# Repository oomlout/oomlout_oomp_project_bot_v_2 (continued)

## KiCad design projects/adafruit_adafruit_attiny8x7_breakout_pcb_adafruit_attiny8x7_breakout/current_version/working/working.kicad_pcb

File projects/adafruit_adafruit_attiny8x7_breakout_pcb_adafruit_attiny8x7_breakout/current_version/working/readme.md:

# adafruit_attiny8x7_breakout_pcb
 
## summary 
* id: adafruit_adafruit_attiny8x7_breakout_pcb_adafruit_attiny8x7_breakout
* user: adafruit
* name: adafruit_attiny8x7_breakout_pcb
* board: adafruit_attiny8x7_breakout
* repo: https://github.com/adafruit/Adafruit-ATtiny8x7-Breakout-PCB

* src_file_repo_sch: 
* src_file_repo_sch_link: https://github.com/adafruit/Adafruit-ATtiny8x7-Breakout-PCB/tree/main/
* full details link: https://github.com/oomlout/oomlout_oomp_project_bot_v_2/tree/main/projects/adafruit_adafruit_attiny8x7_breakout_pcb_adafruit_attiny8x7_breakout/current_version/working  

## schematic  
  
[schematic (pdf)](working_schematic.pdf) 

## pcb  

[board (pdf)](working.pdf)  

## working_bom
| Id | Designator | Footprint | Quantity | Designation | Supplier and ref |  | None | 
| --- | --- | --- | --- | --- | --- | --- | --- | 
| 1 | C5 | 0603-NO | 1 | 0.1uF |  |  | [''] | 
| 2 | U1 | SOT23-5 | 1 | ap2112 |  |  | [''] | 
| 3 | JP3,JP1 | 1X12_ROUND_76MIL | 2 |  |  |  | [''] | 
| 4 | C1 | 0805_10MGAP | 1 | 10uF |  |  | [''] | 
| 5 | R6 | RESPACK_4X0603 | 1 | 10K |  |  | [''] | 
| 6 | D3 | CHIPLED_0603_NOOUTLINE | 1 | GREEN |  |  | [''] | 
| 7 | C3 | 0805-NO | 1 | 10uF |  |  | [''] | 
| 8 | IC2 | QFN24_4MM | 1 | ATTINY8X7-MU |  |  | [''] | 
| 9 | U$12 | PCBFEAT-REV-040 | 1 |  |  |  | [''] | 
| 10 | R1 | 0603-NO | 1 | 10k |  |  | [''] | 
| 11 | CONN3,CONN4 | JST_SH4 | 2 | STEMMA_I2C_QT |  |  | [''] | 
| 12 | D4 | CHIPLED_0603_NOOUTLINE | 1 | red |  |  | [''] | 
| 13 | U$7 | SEESAW_LOGO | 1 |  |  |  | [''] | 
| 14 | SJ1 | SOLDERJUMPER_2WAY_OPEN_NOPASTE | 1 |  |  |  | [''] | 

## bom_schematic
| Ref | Qnty | Value | Cmp name | Footprint | Description | Vendor | DNP | 
| --- | --- | --- | --- | --- | --- | --- | --- | 
| C1 | 1 | 10uF | CAP_CERAMIC0805_10MGAP | working:0805_10MGAP |  |  |  | 
| C3 | 1 | 10uF | CAP_CERAMIC0805-NOOUTLINE | working:0805-NO |  |  |  | 
| C5 | 1 | 0.1uF | CAP_CERAMIC0603_NO | working:0603-NO |  |  |  | 
| CONN3, CONN4 | 2 | STEMMA_I2C_QT | STEMMA_I2C_QT | working:JST_SH4 |  |  |  | 
| D3 | 1 | GREEN | LED0603_NOOUTLINE | working:CHIPLED_0603_NOOUTLINE |  |  |  | 
| D4 | 1 | red | LED0603_NOOUTLINE | working:CHIPLED_0603_NOOUTLINE |  |  |  | 
| IC2 | 1 | ATTINY8X7-MU | ATTINY8X7-MU | working:QFN24_4MM |  |  |  | 
| JP1, JP3 | 2 | HEADER-1X1276MIL | HEADER-1X1276MIL | working:1X12_ROUND_76MIL |  |  |  | 
| R1 | 1 | 10k | RESISTOR_0603_NOOUT | working:0603-NO |  |  |  | 
| R6 | 1 | 10K | RESISTOR_4PACK | working:RESPACK_4X0603 |  |  |  | 
| SJ1 | 1 | SOLDERJUMPER_2WAY | SOLDERJUMPER_2WAY | working:SOLDERJUMPER_2WAY_OPEN_NOPASTE |  |  |  | 
| U1 | 1 | ap2112 | VREG_SOT23-5 | working:SOT23-5 |  |  |  |

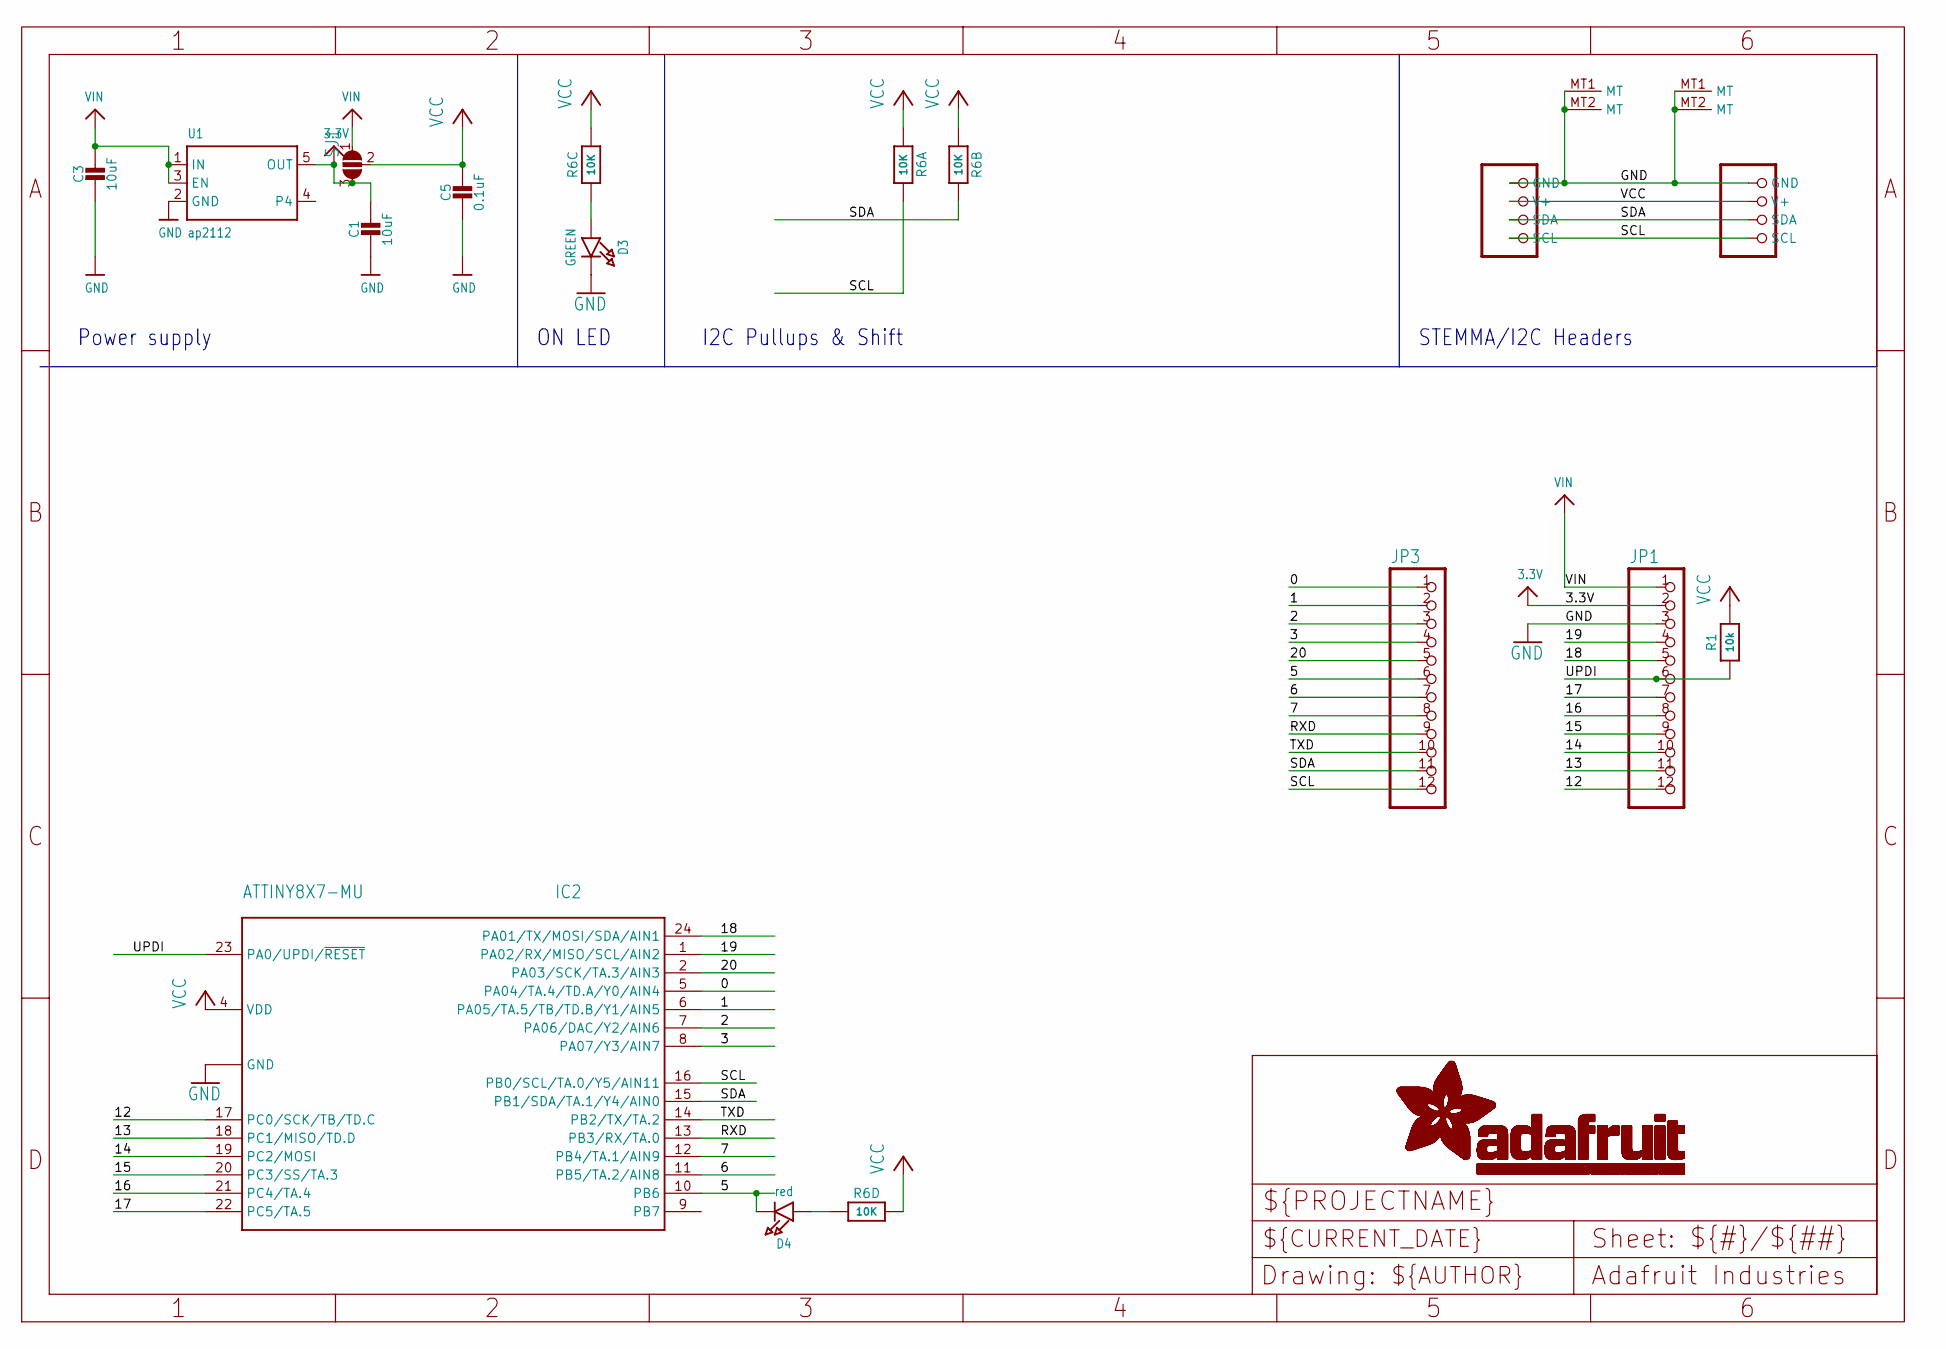
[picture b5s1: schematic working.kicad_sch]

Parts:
C1: 10uF; 0805_10MGAP
C3: 10uF; 0805-NO
C5: 0.1uF; 0603-NO
CONN3, CONN4: STEMMA_I2C_QT; JST_SH4
D3: GREEN; CHIPLED_0603_NOOUTLINE
D4: red; CHIPLED_0603_NOOUTLINE
IC2: ATTINY8X7-MU; QFN24_4MM
JP1, JP3: HEADER-1X1276MIL; 1X12_ROUND_76MIL
R1: 10k; 0603-NO
R6: 10K; RESPACK_4X0603
SJ1: SOLDERJUMPER_2WAY; SOLDERJUMPER_2WAY_OPEN_NOPASTE
U1: ap2112; SOT23-5

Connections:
0: IC2.5 (PA04/TA.4/TD.A/Y0/AIN4), JP3.1
1: IC2.6 (PA05/TA.5/TB/TD.B/Y1/AIN5), JP3.2
2: IC2.7 (PA06/DAC/Y2/AIN6), JP3.3
3: IC2.8 (PA07/Y3/AIN7), JP3.4
3.3V: C1.1, JP1.2, SJ1.3, U1.5 (OUT)
5: D4.C, IC2.10 (PB6), JP3.6
6: IC2.11 (PB5/TA.2/AIN8), JP3.7
7: IC2.12 (PB4/TA.1/AIN9), JP3.8
12: IC2.17 (PC0/SCK/TB/TD.C), JP1.12
13: IC2.18 (PC1/MISO/TD.D), JP1.11
14: IC2.19 (PC2/MOSI), JP1.10
15: IC2.20 (PC3/SS/TA.3), JP1.9
16: IC2.21 (PC4/TA.4), JP1.8
17: IC2.22 (PC5/TA.5), JP1.7
18: IC2.24 (PA01/TX/MOSI/SDA/AIN1), JP1.5
19: IC2.1 (PA02/RX/MISO/SCL/AIN2), JP1.4
20: IC2.2 (PA03/SCK/TA.3/AIN3), JP3.5
GND: C1.2, C3.2, C5.2, CONN3.1 (GND), CONN3.MT1 (MT), CONN3.MT2 (MT), CONN4.1 (GND), CONN4.MT1 (MT), CONN4.MT2 (MT), D3.C, IC2.3 (GND), IC2.THERM (GND), JP1.3, U1.2 (GND)
unnamed: D3.A, R6.3 (1)
unnamed: D4.A, R6.4 (1)
RXD: IC2.13 (PB3/RX/TA.0), JP3.9
SCL: CONN3.4 (SCL), CONN4.4 (SCL), IC2.16 (PB0/SCL/TA.0/Y5/AIN11), JP3.12, R6.8 (2)
SDA: CONN3.3 (SDA), CONN4.3 (SDA), IC2.15 (PB1/SDA/TA.1/Y4/AIN0), JP3.11, R6.7 (2)
TXD: IC2.14 (PB2/TX/TA.2), JP3.10
UPDI: IC2.23 (PA0/UPDI/~RESET), JP1.6, R1.1
VCC: C5.1, CONN3.2 (V+), CONN4.2 (V+), IC2.4 (VDD), R1.2, R6.1, R6.2 (1), R6.5 (2), R6.6 (2), SJ1.2
VIN: C3.1, JP1.1, SJ1.1, U1.1 (IN), U1.3 (EN)

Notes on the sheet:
ON LED
I2C Pullups & Shift
STEMMA/I2C Headers
Power supply

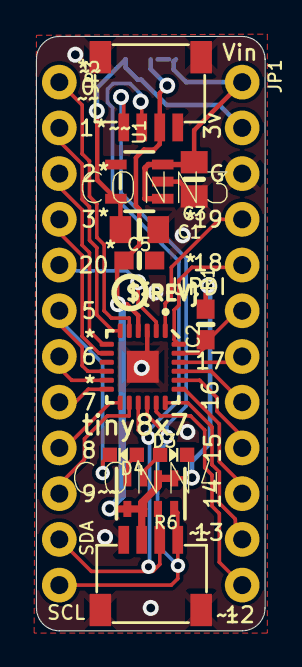
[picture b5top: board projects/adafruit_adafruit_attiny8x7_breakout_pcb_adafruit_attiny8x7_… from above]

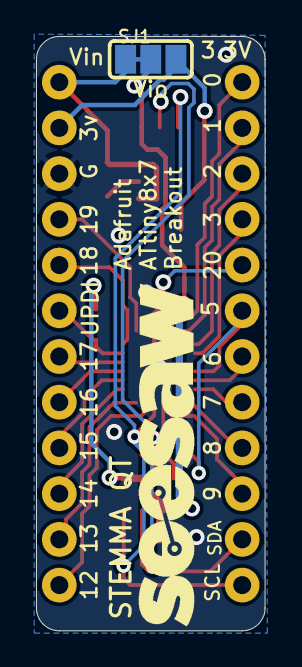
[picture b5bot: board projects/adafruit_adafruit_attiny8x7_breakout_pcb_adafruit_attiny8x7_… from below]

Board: 2 copper layers, 12.7 x 33.0 mm, 16 parts (2 on the bottom side), 27 nets.

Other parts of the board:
U$7: SEESAW_LOGO
U$12: PCBFEAT-REV-040

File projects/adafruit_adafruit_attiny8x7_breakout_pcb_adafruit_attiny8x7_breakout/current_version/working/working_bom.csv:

"Id";"Designator";"Footprint";"Quantity";"Designation";"Supplier and ref";
1;"C5";"0603-NO";1;"0.1uF";;;
2;"U1";"SOT23-5";1;"ap2112";;;
3;"JP3,JP1";"1X12_ROUND_76MIL";2;"";;;
4;"C1";"0805_10MGAP";1;"10uF";;;
5;"R6";"RESPACK_4X0603";1;"10K";;;
6;"D3";"CHIPLED_0603_NOOUTLINE";1;"GREEN";;;
7;"C3";"0805-NO";1;"10uF";;;
8;"IC2";"QFN24_4MM";1;"ATTINY8X7-MU";;;
9;"U$12";"PCBFEAT-REV-040";1;"";;;
10;"R1";"0603-NO";1;"10k";;;
11;"CONN3,CONN4";"JST_SH4";2;"STEMMA_I2C_QT";;;
12;"D4";"CHIPLED_0603_NOOUTLINE";1;"red";;;
13;"U$7";"SEESAW_LOGO";1;"";;;
14;"SJ1";"SOLDERJUMPER_2WAY_OPEN_NOPASTE";1;"";;;

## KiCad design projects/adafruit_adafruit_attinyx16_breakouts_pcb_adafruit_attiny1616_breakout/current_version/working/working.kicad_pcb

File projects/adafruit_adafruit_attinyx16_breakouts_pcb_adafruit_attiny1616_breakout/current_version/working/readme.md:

# adafruit_attinyx16_breakouts_pcb
 
## summary 
* id: adafruit_adafruit_attinyx16_breakouts_pcb_adafruit_attiny1616_breakout
* user: adafruit
* name: adafruit_attinyx16_breakouts_pcb
* board: adafruit_attiny1616_breakout
* repo: https://github.com/adafruit/Adafruit-ATtinyx16-Breakouts-PCB

* src_file_repo_sch: 
* src_file_repo_sch_link: https://github.com/adafruit/Adafruit-ATtinyx16-Breakouts-PCB/tree/main/
* full details link: https://github.com/oomlout/oomlout_oomp_project_bot_v_2/tree/main/projects/adafruit_adafruit_attinyx16_breakouts_pcb_adafruit_attiny1616_breakout/current_version/working  

## schematic  
  
[schematic (pdf)](working_schematic.pdf) 

## pcb  

[board (pdf)](working.pdf)  

## working_bom
| Id | Designator | Footprint | Quantity | Designation | Supplier and ref |  | None | 
| --- | --- | --- | --- | --- | --- | --- | --- | 
| 1 | PLABEL15 | PLABEL15 | 1 |  |  |  | [''] | 
| 2 | D4 | CHIPLED_0603_NOOUTLINE | 1 | Red |  |  | [''] | 
| 3 | PLABEL6 | PLABEL6 | 1 |  |  |  | [''] | 
| 4 | PLABEL100 | PLABEL100 | 1 |  |  |  | [''] | 
| 5 | PLABEL27 | PLABEL27 | 1 |  |  |  | [''] | 
| 6 | PLABEL10 | PLABEL10 | 1 |  |  |  | [''] | 
| 7 | FID2,FID1 | FIDUCIAL_1MM | 2 | FIDUCIAL_1MM |  |  | [''] | 
| 8 | CONN3,CONN4 | JST_SH4 | 2 | STEMMA_I2C_QT |  |  | [''] | 
| 9 | PLABEL12 | PLABEL12 | 1 |  |  |  | [''] | 
| 10 | D3 | CHIPLED_0603_NOOUTLINE | 1 | Green |  |  | [''] | 
| 11 | PLABEL22 | PLABEL22 | 1 |  |  |  | [''] | 
| 12 | PLABEL32 | PLABEL32 | 1 |  |  |  | [''] | 
| 13 | PLABEL0 | PLABEL0 | 1 |  |  |  | [''] | 
| 14 | C5 | 0603-NO | 1 | 0.1uF |  |  | [''] | 
| 15 | JP2,JP4 | 1X10_ROUND70 | 2 |  |  |  | [''] | 
| 16 | PLABEL19 | PLABEL19 | 1 |  |  |  | [''] | 
| 17 | PLABEL1 | PLABEL1 | 1 |  |  |  | [''] | 
| 18 | X1 | QFN20_3MM | 1 | ATTINY8X6_QFN |  |  | [''] | 
| 19 | PLABEL18 | PLABEL18 | 1 |  |  |  | [''] | 
| 20 | PLABEL30 | PLABEL30 | 1 |  |  |  | [''] | 
| 21 | PLABEL2 | PLABEL2 | 1 |  |  |  | [''] | 
| 22 | PLABEL17 | PLABEL17 | 1 |  |  |  | [''] | 
| 23 | PLABEL28 | PLABEL28 | 1 |  |  |  | [''] | 
| 24 | PLABEL33 | PLABEL33 | 1 |  |  |  | [''] | 
| 25 | @HOLE1,@HOLE0 |  | 2 |  |  |  | [''] | 
| 26 | PLABEL29 | PLABEL29 | 1 |  |  |  | [''] | 
| 27 | PLABEL13 | PLABEL13 | 1 |  |  |  | [''] | 
| 28 | PLABEL7 | PLABEL7 | 1 |  |  |  | [''] | 
| 29 | PLABEL3 | PLABEL3 | 1 |  |  |  | [''] | 
| 30 | PLABEL20 | PLABEL20 | 1 |  |  |  | [''] | 
| 31 | R6 | RESPACK_4X0603 | 1 | 10K Pack |  |  | [''] | 
| 32 | PLABEL4 | PLABEL4 | 1 |  |  |  | [''] | 
| 33 | PLABEL21 | PLABEL21 | 1 |  |  |  | [''] | 
| 34 | PLABEL25 | PLABEL25 | 1 |  |  |  | [''] | 
| 35 | PLABEL14 | PLABEL14 | 1 |  |  |  | [''] | 
| 36 | PLABEL5 | PLABEL5 | 1 |  |  |  | [''] | 
| 37 | PLABEL26 | PLABEL26 | 1 |  |  |  | [''] | 
| 38 | PLABEL11 | PLABEL11 | 1 |  |  |  | [''] | 
| 39 | U1 | SOT23-5 | 1 | AP2127K-3.3 |  |  | [''] | 
| 40 | PLABEL23 | PLABEL23 | 1 |  |  |  | [''] | 
| 41 | PLABEL9 | PLABEL9 | 1 |  |  |  | [''] | 
| 42 | PLABEL24 | PLABEL24 | 1 |  |  |  | [''] | 
| 43 | PLABEL31 | PLABEL31 | 1 |  |  |  | [''] | 
| 44 | C3 | 0805-NO | 1 | 10uF |  |  | [''] | 
| 45 | C1 | 0805_10MGAP | 1 | 10uF |  |  | [''] | 
| 46 | PLABEL8 | PLABEL8 | 1 |  |  |  | [''] | 
| 47 | R1 | 0603-NO | 1 | 10K |  |  | [''] | 
| 48 | PLABEL39 | PLABEL39 | 1 |  |  |  | [''] | 
| 49 | PLABEL51 | PLABEL51 | 1 |  |  |  | [''] | 
| 50 | PLABEL54 | PLABEL54 | 1 |  |  |  | [''] | 
| 51 | PLABEL35 | PLABEL35 | 1 |  |  |  | [''] | 
| 52 | PLABEL49 | PLABEL49 | 1 |  |  |  | [''] | 
| 53 | PLABEL43 | PLABEL43 | 1 |  |  |  | [''] | 
| 54 | PLABEL42 | PLABEL42 | 1 |  |  |  | [''] | 
| 55 | PLABEL53 | PLABEL53 | 1 |  |  |  | [''] | 
| 56 | U$12 | PCBFEAT-REV-040 | 1 |  |  |  | [''] | 
| 57 | PLABEL101 | PLABEL101 | 1 |  |  |  | [''] | 
| 58 | PLABEL48 | PLABEL48 | 1 |  |  |  | [''] | 
| 59 | PLABEL46 | PLABEL46 | 1 |  |  |  | [''] | 
| 60 | PLABEL55 | PLABEL55 | 1 |  |  |  | [''] | 
| 61 | PLABEL40 | PLABEL40 | 1 |  |  |  | [''] | 
| 62 | PLABEL38 | PLABEL38 | 1 |  |  |  | [''] | 
| 63 | PLABEL44 | PLABEL44 | 1 |  |  |  | [''] | 
| 64 | U$7 | SEESAW_LOGO | 1 |  |  |  | [''] | 
| 65 | PLABEL47 | PLABEL47 | 1 |  |  |  | [''] | 
| 66 | PLABEL37 | PLABEL37 | 1 |  |  |  | [''] | 
| 67 | PLABEL57 | PLABEL57 | 1 |  |  |  | [''] | 
| 68 | PLABEL41 | PLABEL41 | 1 |  |  |  | [''] | 
| 69 | PLABEL52 | PLABEL52 | 1 |  |  |  | [''] | 
| 70 | PLABEL45 | PLABEL45 | 1 |  |  |  | [''] | 
| 71 | PLABEL58 | PLABEL58 | 1 |  |  |  | [''] | 
| 72 | PLABEL56 | PLABEL56 | 1 |  |  |  | [''] | 
| 73 | PLABEL36 | PLABEL36 | 1 |  |  |  | [''] | 
| 74 | PLABEL50 | PLABEL50 | 1 |  |  |  | [''] | 
| 75 | SJ1 | SOLDERJUMPER_2WAY_OPEN_NOPASTE | 1 |  |  |  | [''] | 

## bom_schematic
| Ref | Qnty | Value | Cmp name | Footprint | Description | Vendor | DNP | 
| --- | --- | --- | --- | --- | --- | --- | --- | 
| C1 | 1 | 10uF | CAP_CERAMIC0805_10MGAP | working:0805_10MGAP |  |  |  | 
| C3 | 1 | 10uF | CAP_CERAMIC0805-NOOUTLINE | working:0805-NO |  |  |  | 
| C5 | 1 | 0.1uF | CAP_CERAMIC0603_NO | working:0603-NO |  |  |  | 
| CONN3, CONN4 | 2 | STEMMA_I2C_QT | STEMMA_I2C_QT | working:JST_SH4 |  |  |  | 
| D3 | 1 | Green | LED0603_NOOUTLINE | working:CHIPLED_0603_NOOUTLINE |  |  |  | 
| D4 | 1 | Red | LED0603_NOOUTLINE | working:CHIPLED_0603_NOOUTLINE |  |  |  | 
| FID1, FID2 | 2 | FIDUCIAL_1MM | FIDUCIAL_1MM | working:FIDUCIAL_1MM |  |  |  | 
| JP2, JP4 | 2 | HEADER-1X1070MIL | HEADER-1X1070MIL | working:1X10_ROUND70 |  |  |  | 
| R1 | 1 | 10K | RESISTOR_0603_NOOUT | working:0603-NO |  |  |  | 
| R6 | 1 | 10K Pack | RESISTOR_4PACK | working:RESPACK_4X0603 |  |  |  | 
| SJ1 | 1 | SOLDERJUMPER_2WAY | SOLDERJUMPER_2WAY | working:SOLDERJUMPER_2WAY_OPEN_NOPASTE |  |  |  | 
| U1 | 1 | AP2127K-3.3 | VREG_SOT23-5 | working:SOT23-5 |  |  |  | 
| X1 | 1 | ATTINY8X6_QFN | ATTINY8X6_QFN | working:QFN20_3MM |  |  |  |

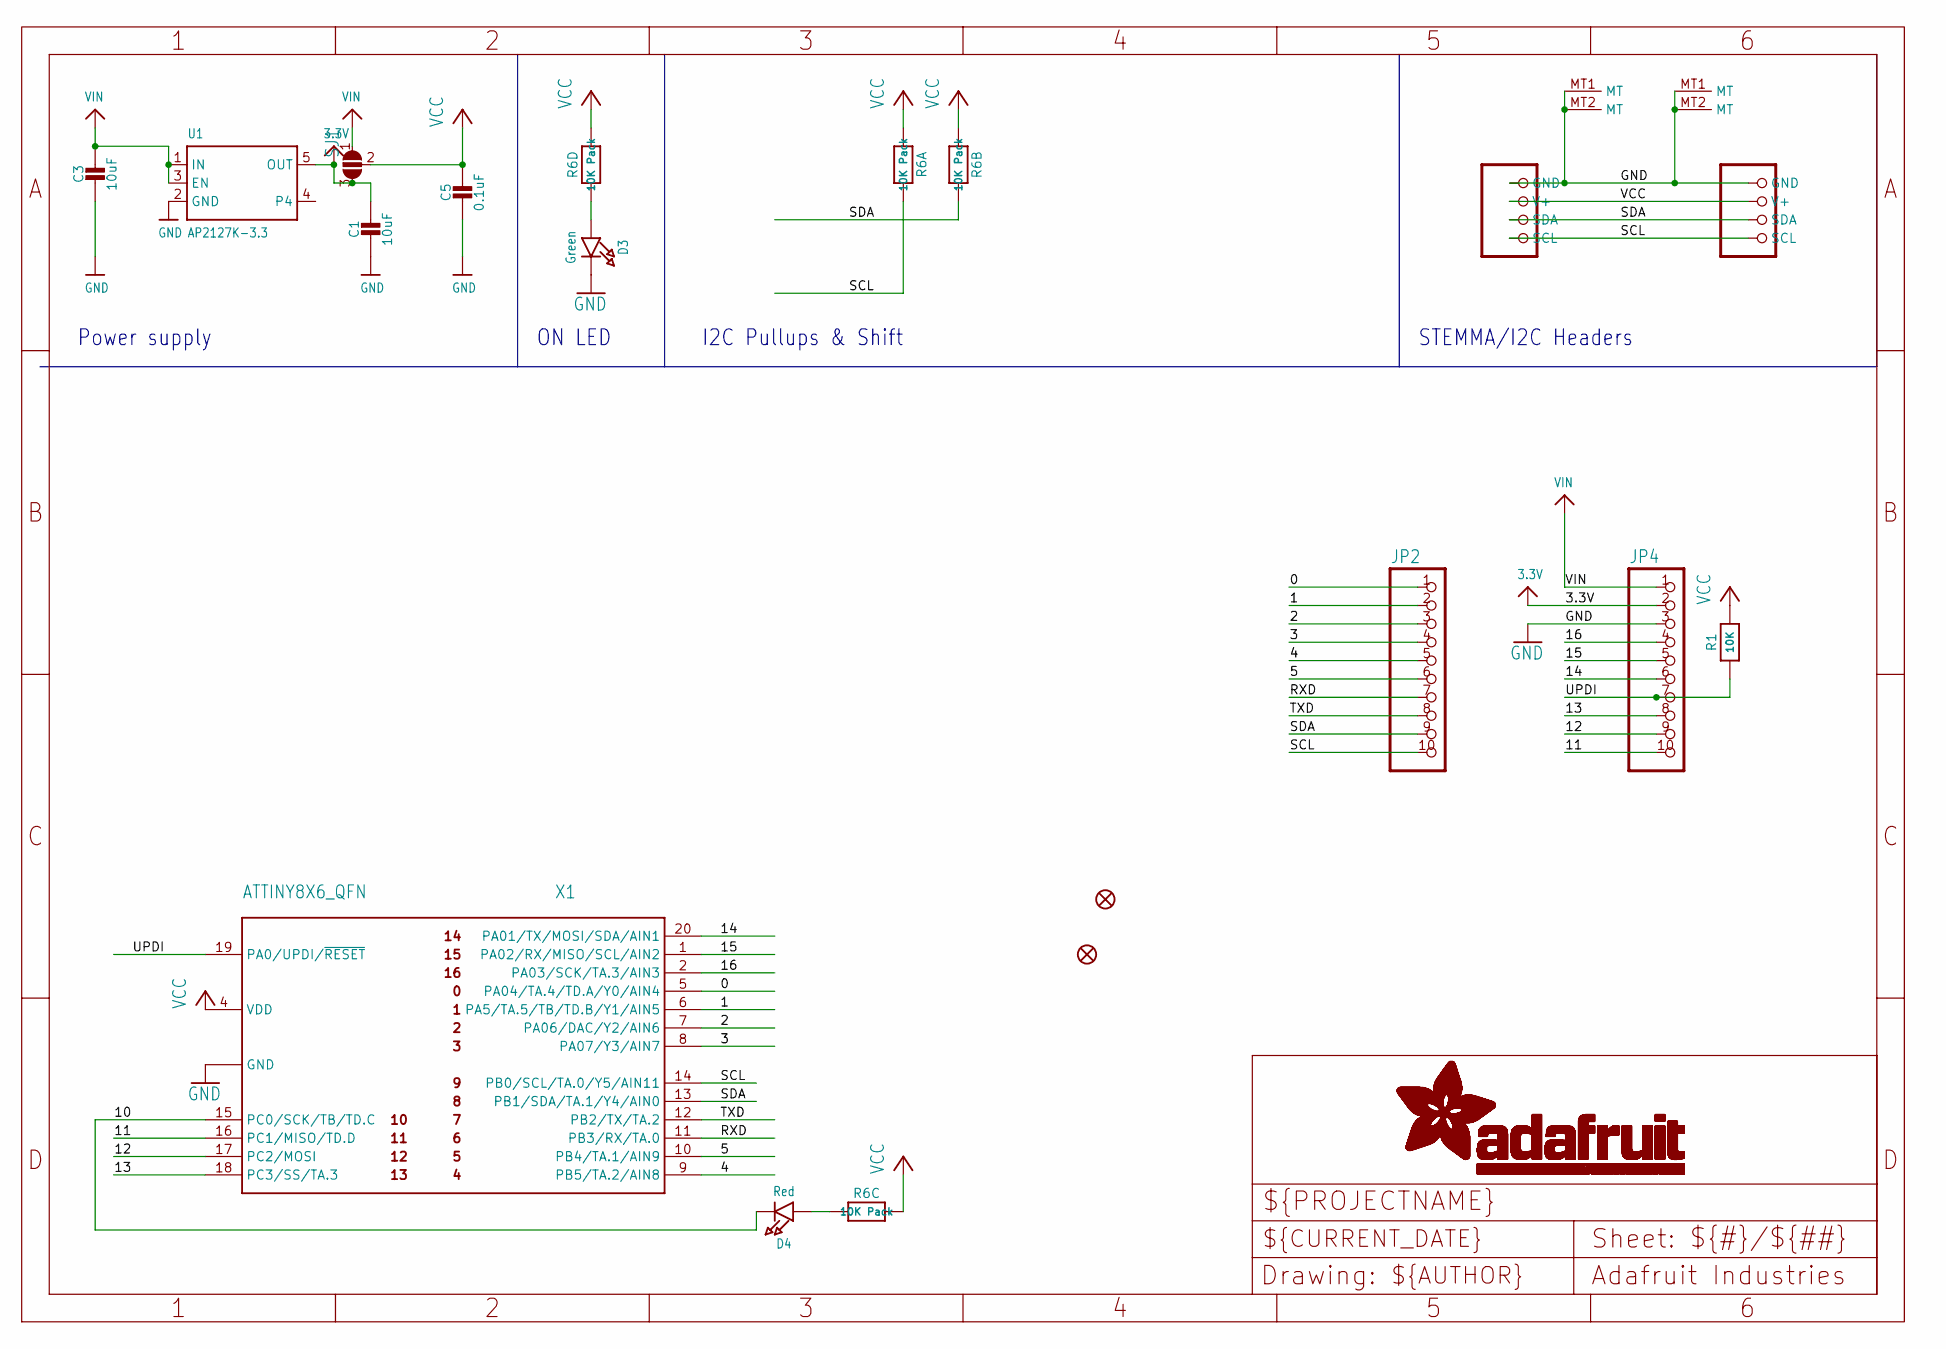
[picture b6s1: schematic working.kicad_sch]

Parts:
C1: 10uF; 0805_10MGAP
C3: 10uF; 0805-NO
C5: 0.1uF; 0603-NO
CONN3, CONN4: STEMMA_I2C_QT; JST_SH4
D3: Green; CHIPLED_0603_NOOUTLINE
D4: Red; CHIPLED_0603_NOOUTLINE
FID1, FID2: FIDUCIAL_1MM
JP2, JP4: HEADER-1X1070MIL; 1X10_ROUND70
R1: 10K; 0603-NO
R6: 10K Pack; RESPACK_4X0603
SJ1: SOLDERJUMPER_2WAY; SOLDERJUMPER_2WAY_OPEN_NOPASTE
U1: AP2127K-3.3; SOT23-5
X1: ATTINY8X6_QFN; QFN20_3MM

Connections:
0: JP2.1, X1.5 (PA04/TA.4/TD.A/Y0/AIN4)
1: JP2.2, X1.6 (PA5/TA.5/TB/TD.B/Y1/AIN5)
2: JP2.3, X1.7 (PA06/DAC/Y2/AIN6)
3: JP2.4, X1.8 (PA07/Y3/AIN7)
3.3V: C1.1, JP4.2, SJ1.3, U1.5 (OUT)
4: JP2.5, X1.9 (PB5/TA.2/AIN8)
5: JP2.6, X1.10 (PB4/TA.1/AIN9)
10: D4.C, X1.15 (PC0/SCK/TB/TD.C)
11: JP4.10, X1.16 (PC1/MISO/TD.D)
12: JP4.9, X1.17 (PC2/MOSI)
13: JP4.8, X1.18 (PC3/SS/TA.3)
14: JP4.6, X1.20 (PA01/TX/MOSI/SDA/AIN1)
15: JP4.5, X1.1 (PA02/RX/MISO/SCL/AIN2)
16: JP4.4, X1.2 (PA03/SCK/TA.3/AIN3)
GND: C1.2, C3.2, C5.2, CONN3.1 (GND), CONN3.MT1 (MT), CONN3.MT2 (MT), CONN4.1 (GND), CONN4.MT1 (MT), CONN4.MT2 (MT), D3.C, JP4.3, U1.2 (GND), X1.3 (GND), X1.PAD (GND)
unnamed: D3.A, R6.4 (1)
unnamed: D4.A, R6.3 (1)
RXD: JP2.7, X1.11 (PB3/RX/TA.0)
SCL: CONN3.4 (SCL), CONN4.4 (SCL), JP2.10, R6.8 (2), X1.14 (PB0/SCL/TA.0/Y5/AIN11)
SDA: CONN3.3 (SDA), CONN4.3 (SDA), JP2.9, R6.7 (2), X1.13 (PB1/SDA/TA.1/Y4/AIN0)
TXD: JP2.8, X1.12 (PB2/TX/TA.2)
UPDI: JP4.7, R1.1, X1.19 (PA0/UPDI/~RESET)
VCC: C5.1, CONN3.2 (V+), CONN4.2 (V+), R1.2, R6.1, R6.2 (1), R6.5 (2), R6.6 (2), SJ1.2, X1.4 (VDD)
VIN: C3.1, JP4.1, SJ1.1, U1.1 (IN), U1.3 (EN)

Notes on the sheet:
ON LED
Power supply
I2C Pullups & Shift
STEMMA/I2C Headers

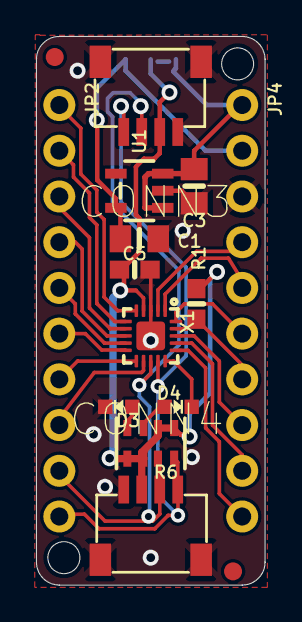
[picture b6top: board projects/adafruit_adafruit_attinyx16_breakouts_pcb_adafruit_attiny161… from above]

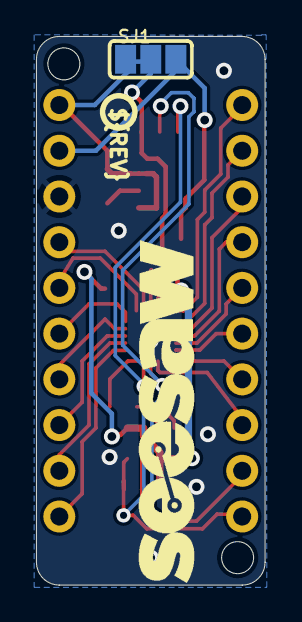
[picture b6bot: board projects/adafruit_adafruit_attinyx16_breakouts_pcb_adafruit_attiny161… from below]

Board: 2 copper layers, 12.7 x 30.5 mm, 79 parts (28 on the bottom side), 24 nets.

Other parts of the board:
@HOLE0, @HOLE1: (no value)
PLABEL0: PLABEL0
PLABEL1: PLABEL1
PLABEL2: PLABEL2
PLABEL3: PLABEL3
PLABEL4: PLABEL4
PLABEL5: PLABEL5
PLABEL6: PLABEL6
PLABEL7: PLABEL7
PLABEL8: PLABEL8
PLABEL9: PLABEL9
PLABEL10: PLABEL10
PLABEL11: PLABEL11
PLABEL12: PLABEL12
PLABEL13: PLABEL13
PLABEL14: PLABEL14
PLABEL15: PLABEL15
PLABEL17: PLABEL17
PLABEL18: PLABEL18
PLABEL19: PLABEL19
PLABEL20: PLABEL20
PLABEL21: PLABEL21
PLABEL22: PLABEL22
PLABEL23: PLABEL23
PLABEL24: PLABEL24
PLABEL25: PLABEL25
PLABEL26: PLABEL26
PLABEL27: PLABEL27
PLABEL28: PLABEL28
PLABEL29: PLABEL29
PLABEL30: PLABEL30
PLABEL31: PLABEL31
PLABEL32: PLABEL32
PLABEL33: PLABEL33
PLABEL35: PLABEL35
PLABEL36: PLABEL36
PLABEL37: PLABEL37
PLABEL38: PLABEL38
PLABEL39: PLABEL39
PLABEL40: PLABEL40
PLABEL41: PLABEL41
PLABEL42: PLABEL42
PLABEL43: PLABEL43
PLABEL44: PLABEL44
PLABEL45: PLABEL45
PLABEL46: PLABEL46
PLABEL47: PLABEL47
PLABEL48: PLABEL48
PLABEL49: PLABEL49
PLABEL50: PLABEL50
PLABEL51: PLABEL51
PLABEL52: PLABEL52
PLABEL53: PLABEL53
PLABEL54: PLABEL54
PLABEL55: PLABEL55
PLABEL56: PLABEL56
PLABEL57: PLABEL57
PLABEL58: PLABEL58
PLABEL100: PLABEL100
PLABEL101: PLABEL101
U$7: SEESAW_LOGO
U$12: PCBFEAT-REV-040

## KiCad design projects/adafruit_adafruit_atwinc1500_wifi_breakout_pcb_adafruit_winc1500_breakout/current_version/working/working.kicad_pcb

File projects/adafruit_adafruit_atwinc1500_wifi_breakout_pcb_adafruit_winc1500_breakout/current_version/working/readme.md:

# adafruit_atwinc1500_wifi_breakout_pcb
 
## summary 
* id: adafruit_adafruit_atwinc1500_wifi_breakout_pcb_adafruit_winc1500_breakout
* user: adafruit
* name: adafruit_atwinc1500_wifi_breakout_pcb
* board: adafruit_winc1500_breakout
* repo: https://github.com/adafruit/Adafruit-ATWINC1500-WiFi-Breakout-PCB

* src_file_repo_sch: 
* src_file_repo_sch_link: https://github.com/adafruit/Adafruit-ATWINC1500-WiFi-Breakout-PCB/tree/master/
* full details link: https://github.com/oomlout/oomlout_oomp_project_bot_v_2/tree/main/projects/adafruit_adafruit_atwinc1500_wifi_breakout_pcb_adafruit_winc1500_breakout/current_version/working  

## schematic  
  
[schematic (pdf)](working_schematic.pdf) 

## pcb  

[board (pdf)](working.pdf)  

## working_bom
| Id | Designator | Footprint | Quantity | Designation | Supplier and ref |  | None | 
| --- | --- | --- | --- | --- | --- | --- | --- | 
| 1 | U1 | TSSOP20 | 1 | 74LVC245 |  |  | [''] | 
| 2 | U$4 | ADAFRUIT_5MM | 1 |  |  |  | [''] | 
| 3 | U$1 | ATWINC1500_MR210PA | 1 | ATWINC1500_MR210PB |  |  | [''] | 
| 4 | C1,C3 | 0805-NO | 2 | 10uF |  |  | [''] | 
| 5 | R3,R7 | _0805MP | 2 | 100K |  |  | [''] | 
| 6 | R2,R1 | 0805-NO | 2 | 100K |  |  | [''] | 
| 7 | FID1,FID2 | FIDUCIAL_1MM | 2 | FIDUCIAL" |  |  | [''] | 
| 8 | U2 | SOT23-5 | 1 | AP2112-3.3 |  |  | [''] | 
| 9 | U$3,U$2 | MOUNTINGHOLE_2.5_PLATED | 2 | MOUNTINGHOLE2.5 |  |  | [''] | 
| 10 | JP2 | 1X13_ROUND_70 | 1 |  |  |  | [''] | 
| 11 | C2 | 0805_10MGAP | 1 | 10uF |  |  | [''] | 
| 12 | D1 | CHIPLED_0805_NOOUTLINE | 1 | green |  |  | [''] | 
| 13 | C4 | 0805-NO | 1 | 0.1uF |  |  | [''] | 
| 14 | D3 | CHIPLED_0805_NOOUTLINE | 1 | Red |  |  | [''] | 
| 15 | U$5 | PCBFEAT-REV-040 | 1 |  |  |  | [''] | 
| 16 | D2 | CHIPLED_0805_NOOUTLINE | 1 | Yellow |  |  | [''] | 
| 17 | R8 | RESPACK_4X0603 | 1 | 1K |  |  | [''] | 
| 18 | U$6 | ADAFRUIT_TEXT_20MM | 1 |  |  |  | [''] | 

## bom_schematic
| Ref | Qnty | Value | Cmp name | Footprint | Description | Vendor | DNP | 
| --- | --- | --- | --- | --- | --- | --- | --- | 
| C1, C3 | 2 | 10uF | CAP_CERAMIC0805-NOOUTLINE | working:0805-NO |  |  |  | 
| C2 | 1 | 10uF | CAP_CERAMIC0805_10MGAP | working:0805_10MGAP |  |  |  | 
| C4 | 1 | 0.1uF | CAP_CERAMIC0805-NOOUTLINE | working:0805-NO |  |  |  | 
| D1 | 1 | green | LED0805_NOOUTLINE | working:CHIPLED_0805_NOOUTLINE |  |  |  | 
| D2 | 1 | Yellow | LED0805_NOOUTLINE | working:CHIPLED_0805_NOOUTLINE |  |  |  | 
| D3 | 1 | Red | LED0805_NOOUTLINE | working:CHIPLED_0805_NOOUTLINE |  |  |  | 
| FID1, FID2 | 2 | FIDUCIAL"" | FIDUCIAL{dblquote}{dblquote} | working:FIDUCIAL_1MM |  |  |  | 
| JP2 | 1 | HEADER-1X13 | HEADER-1X13 | working:1X13_ROUND_70 |  |  |  | 
| R1, R2 | 2 | 100K | RESISTOR0805_NOOUTLINE | working:0805-NO |  |  |  | 
| R3, R7 | 2 | 100K | RESISTOR_0805MP | working:_0805MP |  |  |  | 
| R8 | 1 | 1K | RESISTOR_4PACK | working:RESPACK_4X0603 |  |  |  | 
| U1 | 1 | 74LVC245 | 74LCX245 | working:TSSOP20 |  |  |  | 
| U2 | 1 | AP2112-3.3 | VREG_SOT23-5 | working:SOT23-5 |  |  |  | 
| U$1 | 1 | ATWINC1500_MR210PA | ATWINC1500_MR210PA | working:ATWINC1500_MR210PA |  |  |  | 
| U$2, U$3 | 2 | MOUNTINGHOLE2.5 | MOUNTINGHOLE2.5 | working:MOUNTINGHOLE_2.5_PLATED |  |  |  | 

## mounting_holes
| x | y | package | value | ref | size | 
| --- | --- | --- | --- | --- | --- | 
| 0.0 | 0.0 | MOUNTINGHOLE_2.5_PLATED | MOUNTINGHOLE2.5 | U$2 | m3 | 
| 27.94 | 0.0 | MOUNTINGHOLE_2.5_PLATED | MOUNTINGHOLE2.5 | U$3 | m3 |

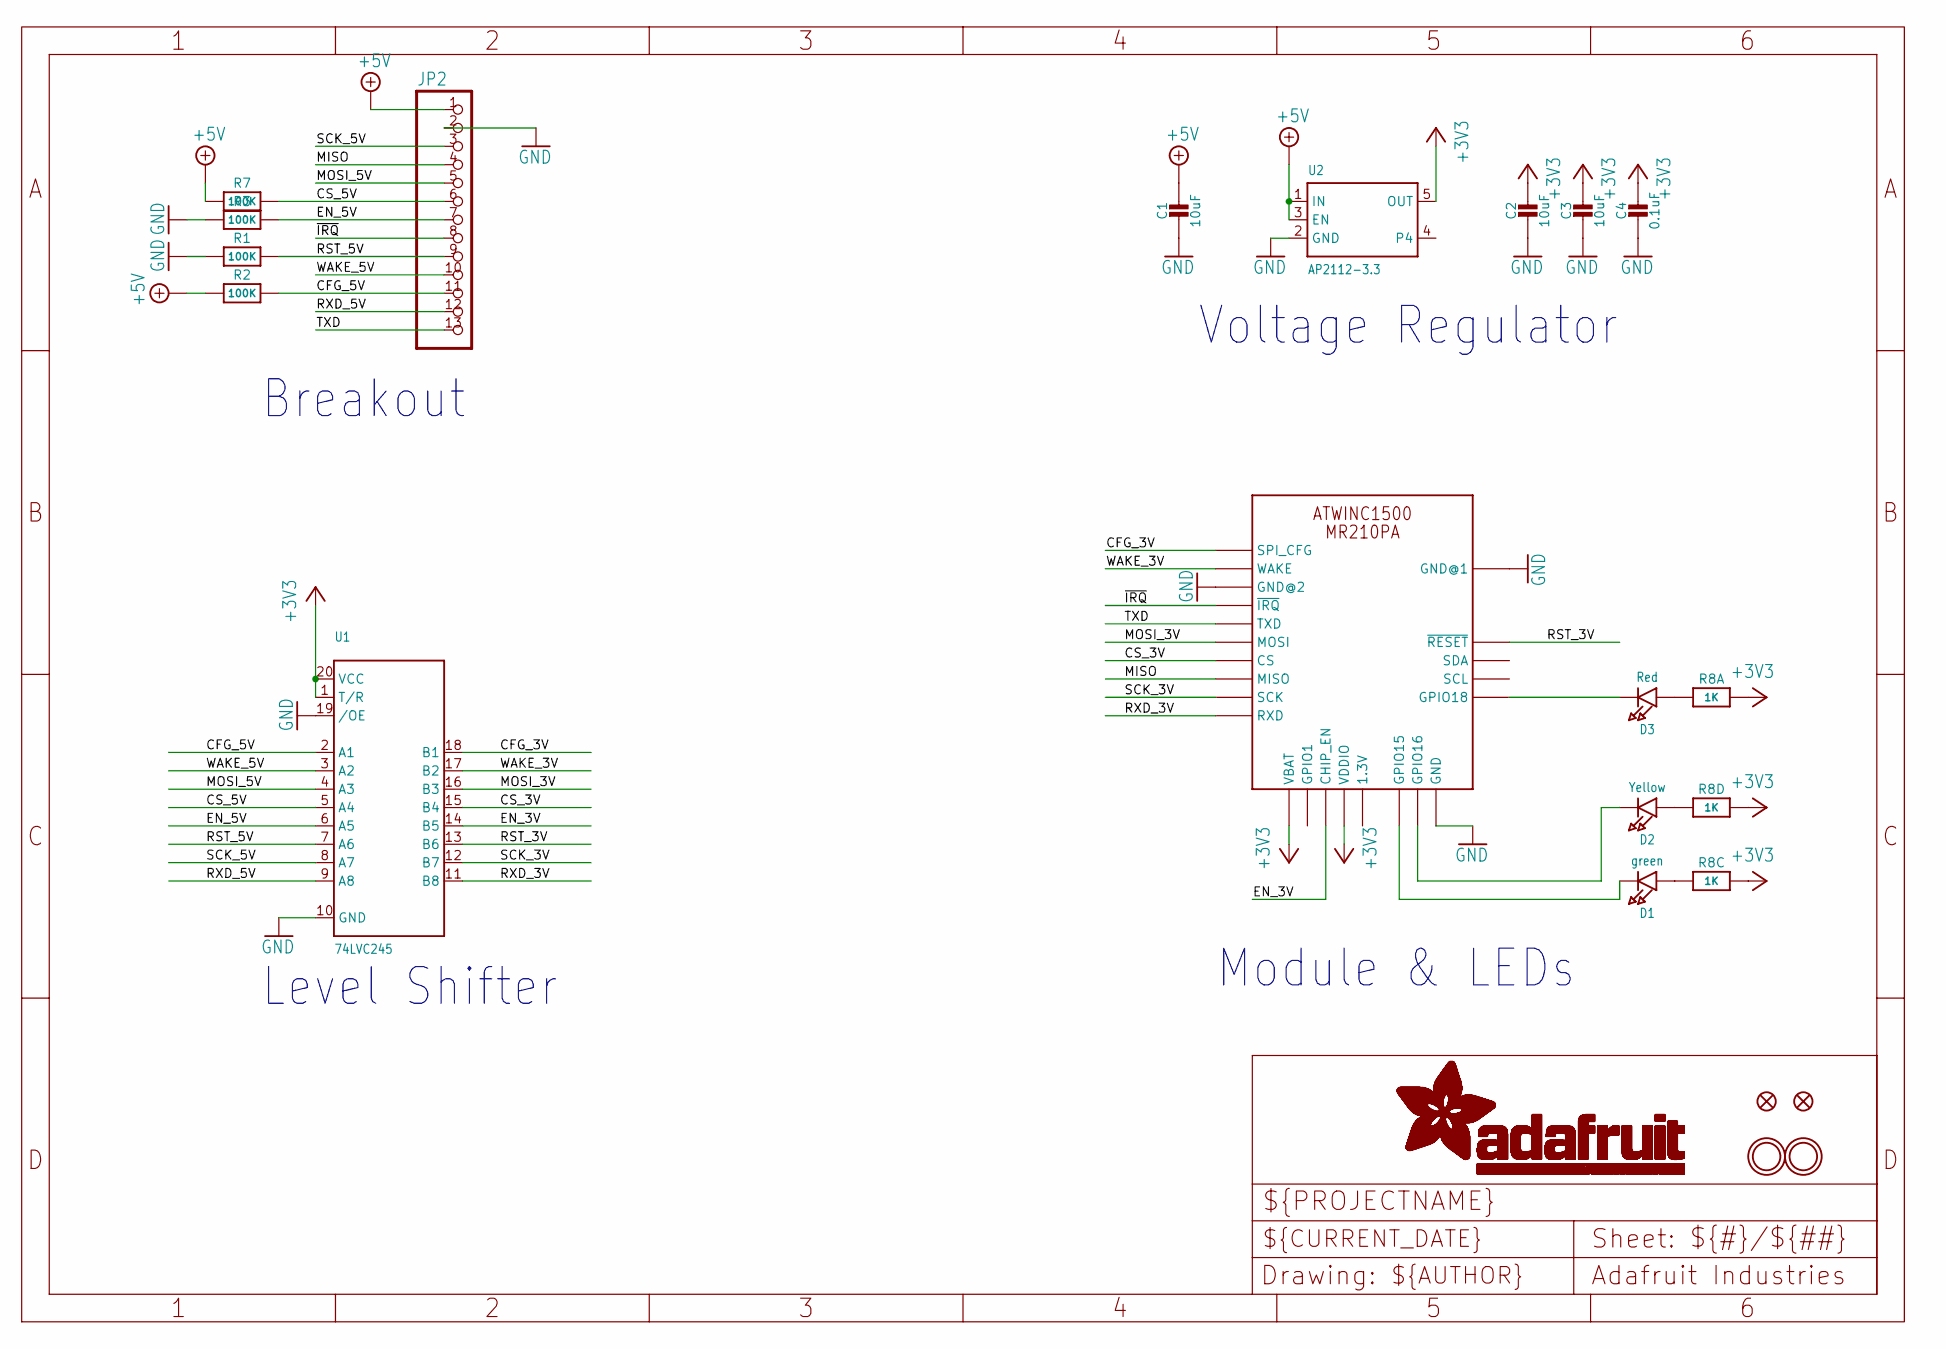
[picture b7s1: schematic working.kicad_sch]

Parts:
C1, C3: 10uF; 0805-NO
C2: 10uF; 0805_10MGAP
C4: 0.1uF; 0805-NO
D1: green; CHIPLED_0805_NOOUTLINE
D2: Yellow; CHIPLED_0805_NOOUTLINE
D3: Red; CHIPLED_0805_NOOUTLINE
FID1, FID2: FIDUCIAL""; FIDUCIAL_1MM
JP2: HEADER-1X13; 1X13_ROUND_70
R1, R2: 100K; 0805-NO
R3, R7: 100K; _0805MP
R8: 1K; RESPACK_4X0603
U1: 74LVC245; TSSOP20
U2: AP2112-3.3; SOT23-5
U$1: ATWINC1500_MR210PA
U$2, U$3: MOUNTINGHOLE2.5; MOUNTINGHOLE_2.5_PLATED

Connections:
+3V3: C2.1, C3.1, C4.1, R8.5 (2), R8.6 (2), R8.8 (2), U1.1 (T/R), U1.20 (VCC), U2.5 (OUT), U$1.J20 (VBAT), U$1.J23 (VDDIO)
+5V: C1.1, JP2.1, R2.1, R7.1, U2.1 (IN), U2.3 (EN)
CFG_3V: U1.18 (B1), U$1.J10 (SPI_CFG)
CFG_5V: JP2.11, R2.2, U1.2 (A1)
CS_3V: U1.15 (B4), U$1.J16 (CS)
CS_5V: JP2.6, R7.2, U1.5 (A4)
EN_3V: U1.14 (B5), U$1.J22 (CHIP_EN)
EN_5V: JP2.7, R3.2, U1.6 (A5)
GND: C1.2, C2.2, C3.2, C4.2, JP2.2, R1.1, R3.1, U1.10 (GND), U1.19 (/OE), U2.2 (GND), U$1.J9 (GND@1), U$1.J12 (GND@2), U$1.J28 (GND), U$1.MTGND (GND)
GPIO15: D1.C, U$1.J26 (GPIO15)
GPIO16: D2.C, U$1.J27 (GPIO16)
GPIO18: D3.C, U$1.J1 (GPIO18)
MISO: JP2.4, U$1.J17 (MISO)
MOSI_3V: U1.16 (B3), U$1.J15 (MOSI)
MOSI_5V: JP2.5, U1.4 (A3)
unnamed: D3.A, R8.1
unnamed: D2.A, R8.4 (1)
unnamed: D1.A, R8.3 (1)
RST_3V: U1.13 (B6), U$1.J4 (~RESET)
RST_5V: JP2.9, R1.2, U1.7 (A6)
RXD_3V: U1.11 (B8), U$1.J19 (RXD)
RXD_5V: JP2.12, U1.9 (A8)
SCK_3V: U1.12 (B7), U$1.J18 (SCK)
SCK_5V: JP2.3, U1.8 (A7)
TXD: JP2.13, U$1.J14 (TXD)
WAKE_3V: U1.17 (B2), U$1.J11 (WAKE)
WAKE_5V: JP2.10, U1.3 (A2)
~IRQ: JP2.8, U$1.J13 (~IRQ)

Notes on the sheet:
Module & LEDs
Voltage Regulator
Level Shifter
Breakout

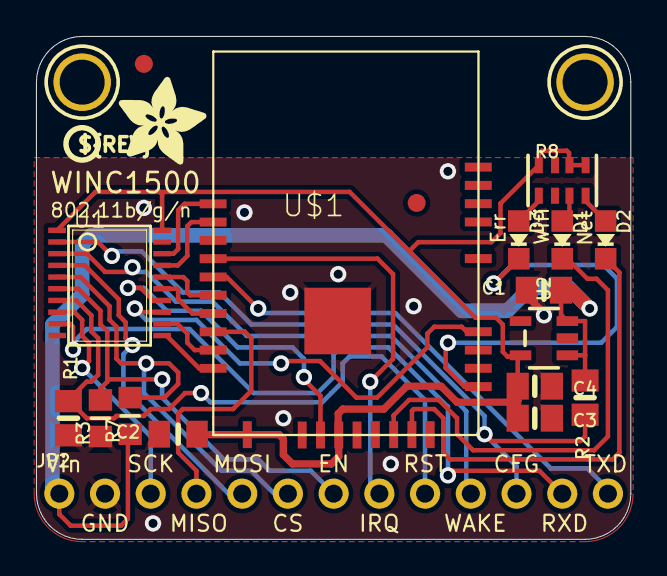
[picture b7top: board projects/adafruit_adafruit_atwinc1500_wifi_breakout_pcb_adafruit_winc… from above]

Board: 2 copper layers, 33.0 x 27.9 mm, 23 parts (1 on the bottom side), 28 nets.

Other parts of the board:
U$4: ADAFRUIT_5MM
U$5: PCBFEAT-REV-040
U$6: ADAFRUIT_TEXT_20MM
